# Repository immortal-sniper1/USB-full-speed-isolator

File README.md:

# USB full speed isolator
 Simple open source USB full speed isolator.

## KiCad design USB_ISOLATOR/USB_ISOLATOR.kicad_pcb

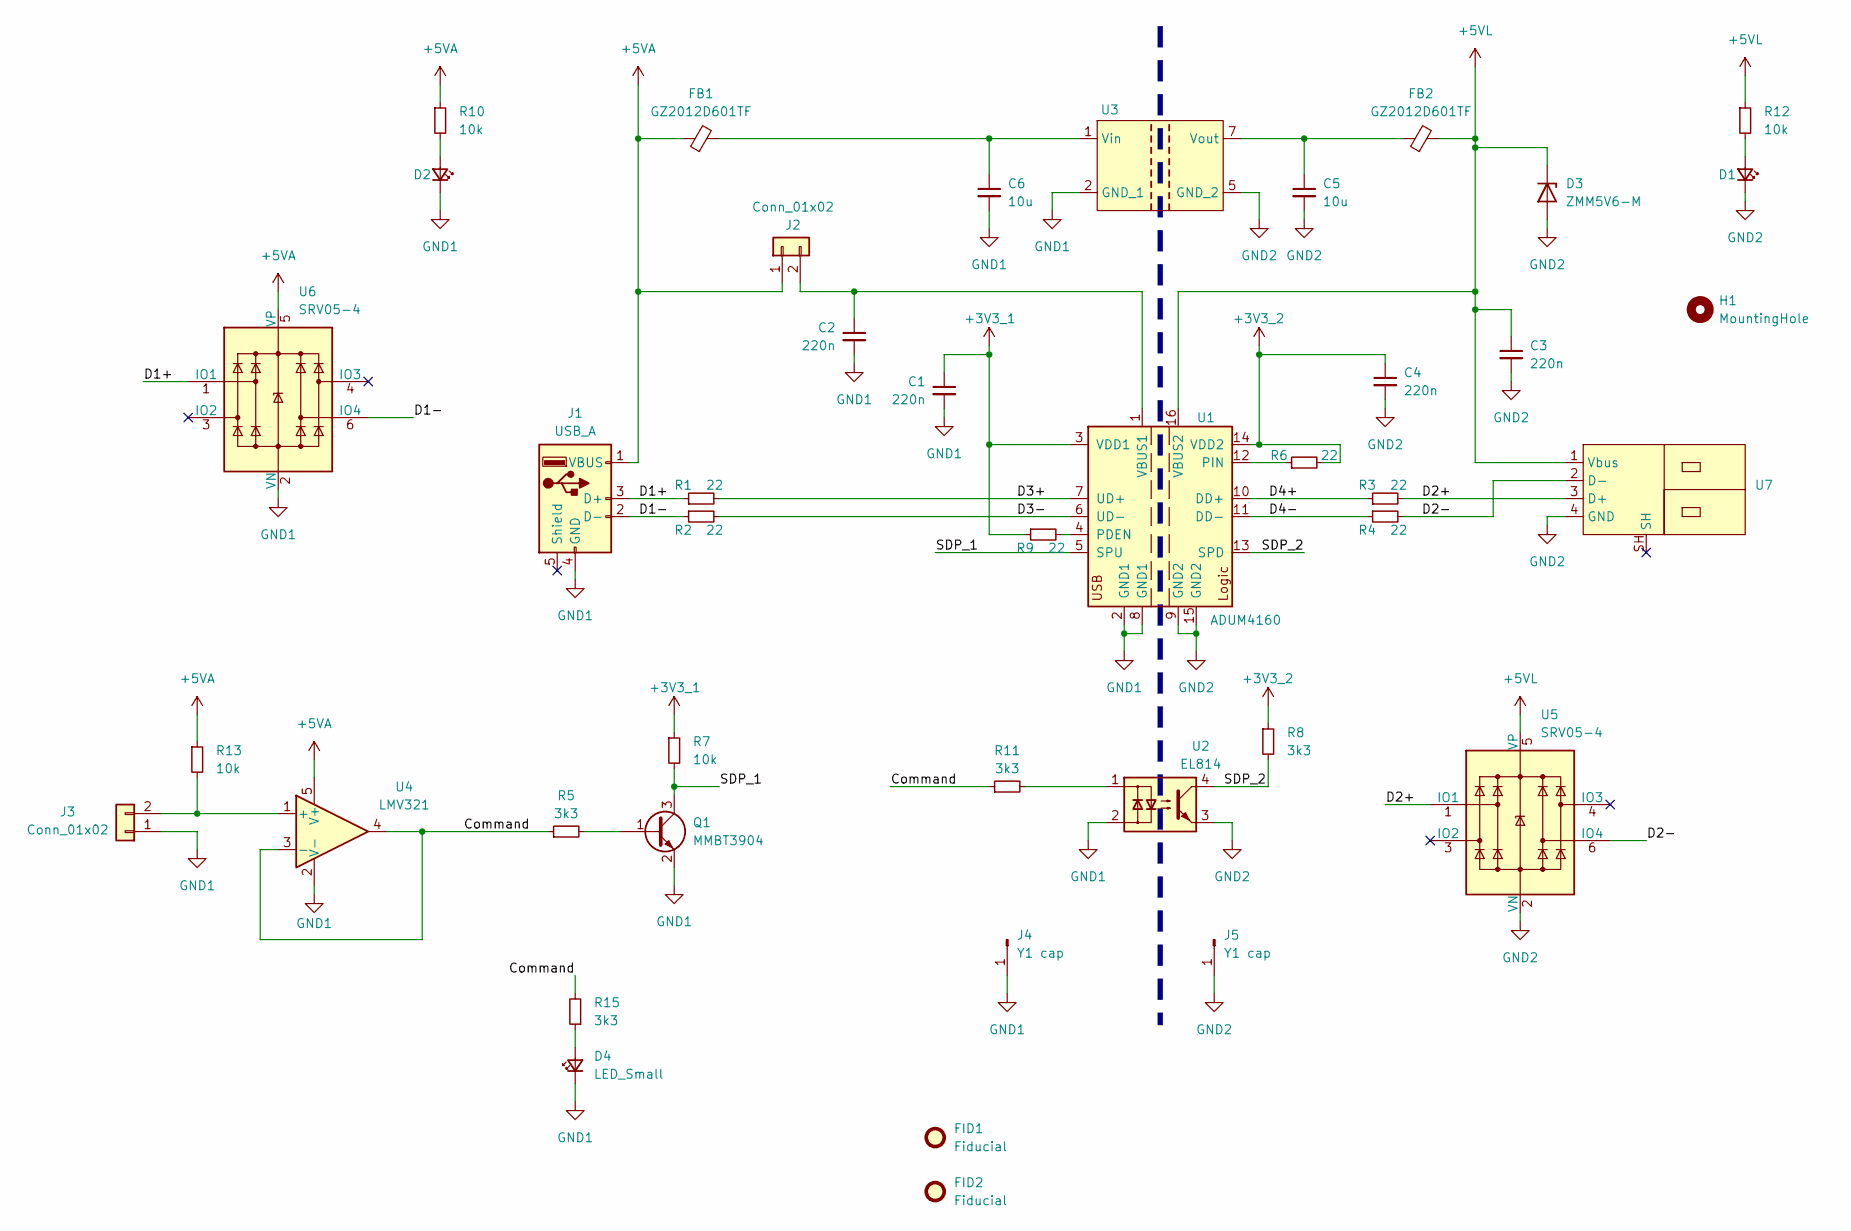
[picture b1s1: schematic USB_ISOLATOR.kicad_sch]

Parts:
C1, C2, C3, C4: 220n; C_0603_1608Metric; LCSC C21120
C5, C6: 10u; C_0805_2012Metric; LCSC C15850
D1, D2: green; LED_0805_2012Metric; LCSC C2297
D3: ZMM5V6-M; D_MiniMELF; LCSC C8062
D4: LED_Small; LED_0805_2012Metric; LCSC C2297
FB1, FB2: GZ2012D601TF; L_0805_2012Metric_Pad1.05x1.20mm_HandSolder; LCSC C1017
FID1: Fiducial; OSHW-Logo2_9.8x8mm_SilkScreen
FID2: Fiducial; KiCad-Logo_5mm_SilkScreen
H1: MountingHole; MountingHole_3mm
J1: USB_A; USB_A_Molex_67643_Horizontal
J2, J3: Conn_01x02; PinHeader_1x03_P2.54mm_Vertical
J4, J5: Y1 cap; PinHeader_1x01_P2.54mm_Vertical
Q1: MMBT3904; SOT-23; LCSC C20526
R1, R2, R3, R4, R6, R9: 22; R_0402_1005Metric_Pad0.72x0.64mm_HandSolder; LCSC C25092
R5, R8, R11, R15: 3k3; R_0603_1608Metric; LCSC C22978
R7, R10, R12, R13: 10k; R_0603_1608Metric; LCSC C25804
U1: ADUM4160; SOIC-16W_7.5x10.3mm_P1.27mm; LCSC C57791
U2: EL814; SMDIP-4_W9.53mm; LCSC C106900
U3: SIP7_DCDC single
U4: LMV321; SOT-23-5_HandSoldering; LCSC C7972
U5, U6: SRV05-4; SOT-23-6; LCSC C85364
U7: USB A male SMD; LCSC C386752

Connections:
+3V3_1: C1.1, R7.1, R9.1, U1.3 (VDD1)
+3V3_2: C4.1, R6.2, R8.1, U1.14 (VDD2)
+5VA: FB1.1, J1.1 (VBUS), J2.1, R10.1, R13.1, U4.5 (V+), U6.5 (VP)
+5VL: C3.1, D3.1 (K), FB2.2, R12.1, U1.16 (VBUS2), U5.5 (VP), U7.1 (Vbus)
/Command: R5.1, R11.1, R15.2, U4.3 (-), U4.4
/D1+: J1.3 (D+), R1.1, U6.1 (IO1)
/D1-: J1.2 (D-), R2.1, U6.6 (IO4)
/D2+: R3.2, U5.1 (IO1), U7.3 (D+)
/D2-: R4.2, U5.6 (IO4), U7.2 (D-)
/D3+: R1.2, U1.7 (UD+)
/D3-: R2.2, U1.6 (UD-)
/D4+: R3.1, U1.10 (DD+)
/D4-: R4.1, U1.11 (DD-)
/SDP_1: Q1.3 (C), R7.2, U1.5 (SPU)
/SDP_2: R8.2, U1.13 (SPD), U2.4
GND1: C1.2, C2.2, C6.2, D2.1 (K), D4.1 (K), J1.4 (GND), J3.1, J4.1, Q1.2 (E), U1.2 (GND1), U1.8 (GND1), U2.2, U3.2 (GND_1), U4.2 (V-), U6.2 (VN)
GND2: C3.2, C4.2, C5.2, D1.1 (K), D3.2 (A), J5.1, U1.9 (GND2), U1.15 (GND2), U2.3, U3.5 (GND_2), U5.2 (VN), U7.4 (GND)
unnamed: D1.2 (A), R12.2
unnamed: D2.2 (A), R10.2
unnamed: D4.2 (A), R15.1
unnamed: C2.1, J2.2, U1.1 (VBUS1)
unnamed: J3.2, R13.2, U4.1 (+)
unnamed: Q1.1 (B), R5.2
unnamed: R11.2, U2.1
unnamed: R9.2, U1.4 (PDEN)
unnamed: R6.1, U1.12 (PIN)
unnamed: C6.1, FB1.2, U3.1 (Vin)
unnamed: C5.1, FB2.1, U3.7 (Vout)

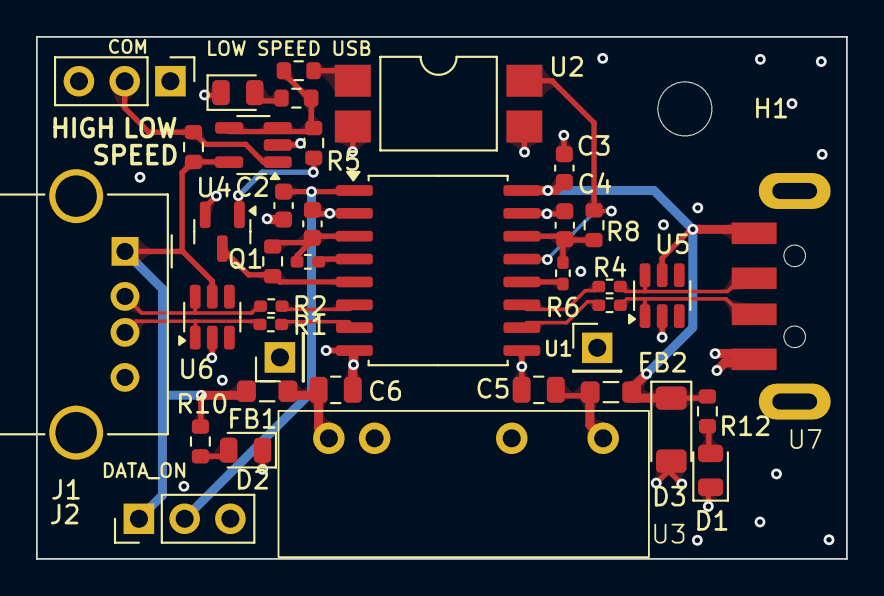
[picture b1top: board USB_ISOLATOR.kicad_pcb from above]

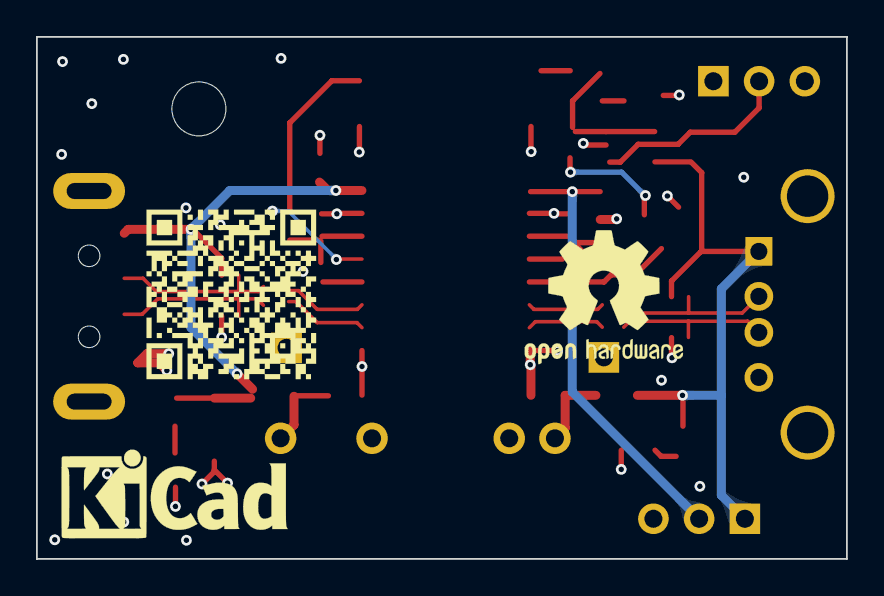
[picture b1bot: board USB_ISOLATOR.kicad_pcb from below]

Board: 4 copper layers, 45.0 x 29.0 mm, 42 parts (2 on the bottom side), 28 nets.

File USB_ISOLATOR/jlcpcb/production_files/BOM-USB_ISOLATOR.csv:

Comment,Designator,Footprint,LCSC
GZ2012D601TF,"FB1,FB2",L_0805_2012Metric_Pad1.05x1.20mm_HandSolder,C1017
EL814,U2,SMDIP-4_W9.53mm,C106900
10u,"C5,C6",C_0805_2012Metric,C15850
MMBT3904,Q1,SOT-23,C20526
220n,"C1,C2,C3,C4",C_0603_1608Metric,C21120
green,"D1,D2,D4",LED_0805_2012Metric,C2297
3k3,"R11,R15,R5,R8",R_0603_1608Metric,C22978
22,"R1,R2,R3,R4,R6,R9",R_0402_1005Metric_Pad0.72x0.64mm_HandSolder,C25092
10k,"R10,R12,R13,R7",R_0603_1608Metric,C25804
~,U7,USB A male SMD,C386752
ADUM4160,U1,SOIC-16W_7.5x10.3mm_P1.27mm,C57791
LMV321,U4,SOT-23-5_HandSoldering,C7972
ZMM5V6-M,D3,D_MiniMELF,C8062
SRV05-4,"U5,U6",SOT-23-6,C85364
Conn_01x02,J3,PinHeader_1x03_P2.54mm_Vertical,
USB_A,J1,USB_A_Molex_67643_Horizontal,
~,U3,SIP7_DCDC single,
Fiducial,FID2,KiCad-Logo_5mm_SilkScreen,
Fiducial,FID1,OSHW-Logo2_9.8x8mm_SilkScreen,
Conn_01x02,J2,PinHeader_1x03_P2.54mm_Vertical,
Y1 cap,J5,PinHeader_1x01_P2.54mm_Vertical,
Y1 cap,J4,PinHeader_1x01_P2.54mm_Vertical,
